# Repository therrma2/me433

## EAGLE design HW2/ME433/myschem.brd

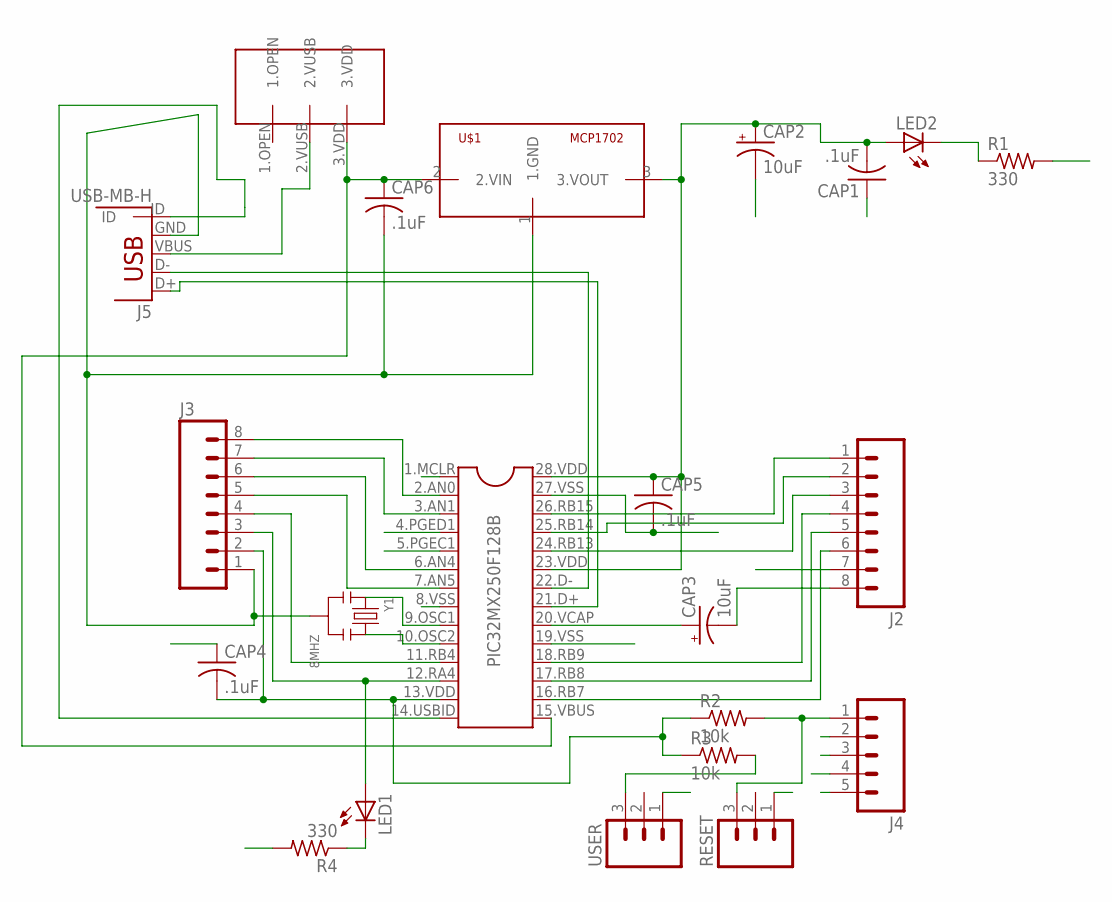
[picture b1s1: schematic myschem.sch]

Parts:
CAP1, CAP4, CAP5, CAP6: .1uF; C025-024X044
CAP2, CAP3: 10uF; B45181B
J2, J3: M08; 1X08_ROUND
J4: M05PTH; 1X05
J5: USB-MB-H
LED1, LED2: LED3MM
PIC32MX250F128B: DIL28-3
R1, R4: 330; 0207/10
R2, R3: 10k; 0207/10
RESET: M03PTH; 1X03
U$1: MCP1702; TO92
U$2: SLIDE-SWTICH; SLIDE-SWITCH
USER: M03PTH; 1X03
Y1: 8MHZ; X3-2.5-8X3X5.5MM

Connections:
GND: CAP1.1, CAP2.-, CAP3.-, CAP4.1, CAP5.2, CAP6.2, J2.8, J3.1, J4.3, J5.GND, PIC32MX250F128B.8.VSS (8), PIC32MX250F128B.19.VSS (19), PIC32MX250F128B.27.VSS (27), R1.2, R4.2, RESET.1, U$1.1 (1.GND), USER.1, Y1.2
MCLR: J4.1, PIC32MX250F128B.1.MCLR (1), R2.2, RESET.3
unnamed: J3.8, PIC32MX250F128B.2.AN0 (2)
unnamed: J3.7, PIC32MX250F128B.3.AN1 (3)
unnamed: J3.6, PIC32MX250F128B.6.AN4 (6)
unnamed: J3.5, PIC32MX250F128B.7.AN5 (7)
unnamed: J5.D-, PIC32MX250F128B.22.D- (22)
unnamed: J5.D+, PIC32MX250F128B.21.D+ (21)
unnamed: J3.3, LED1.A, PIC32MX250F128B.12.RA4 (12)
unnamed: J5.ID, PIC32MX250F128B.14.USBID (14)
unnamed: PIC32MX250F128B.9.OSC1 (9), Y1.1
unnamed: PIC32MX250F128B.10.OSC2 (10), Y1.3
unnamed: LED2.K (C), R1.1
unnamed: J5.VBUS, U$2.2.VUSB
unnamed: J2.6, PIC32MX250F128B.16.RB7 (16)
unnamed: LED1.K (C), R4.1
unnamed: J2.1, PIC32MX250F128B.26.RB15 (26)
unnamed: J2.2, PIC32MX250F128B.25.RB14 (25)
unnamed: J2.3, PIC32MX250F128B.24.RB13 (24)
unnamed: J2.4, PIC32MX250F128B.18.RB9 (18)
unnamed: J2.5, PIC32MX250F128B.17.RB8 (17)
unnamed: CAP3.+, PIC32MX250F128B.20.VCAP (20)
PGEC1: J4.5, PIC32MX250F128B.5.PGEC1 (5)
PGED1: J4.4, PIC32MX250F128B.4.PGED1 (4)
USER: J3.4, PIC32MX250F128B.11.RB4 (11), R3.2, USER.3
VBUS: CAP6.1, J2.7, PIC32MX250F128B.15.VBUS (15), U$1.2 (2.VIN), U$2.3.VDD
VDD: CAP1.2, CAP2.+, CAP4.2, CAP5.1, J3.2, J4.2, LED2.A, PIC32MX250F128B.13.VDD (13), PIC32MX250F128B.23.VDD (23), PIC32MX250F128B.28.VDD (28), R2.1, R3.1, U$1.3 (3.VOUT)

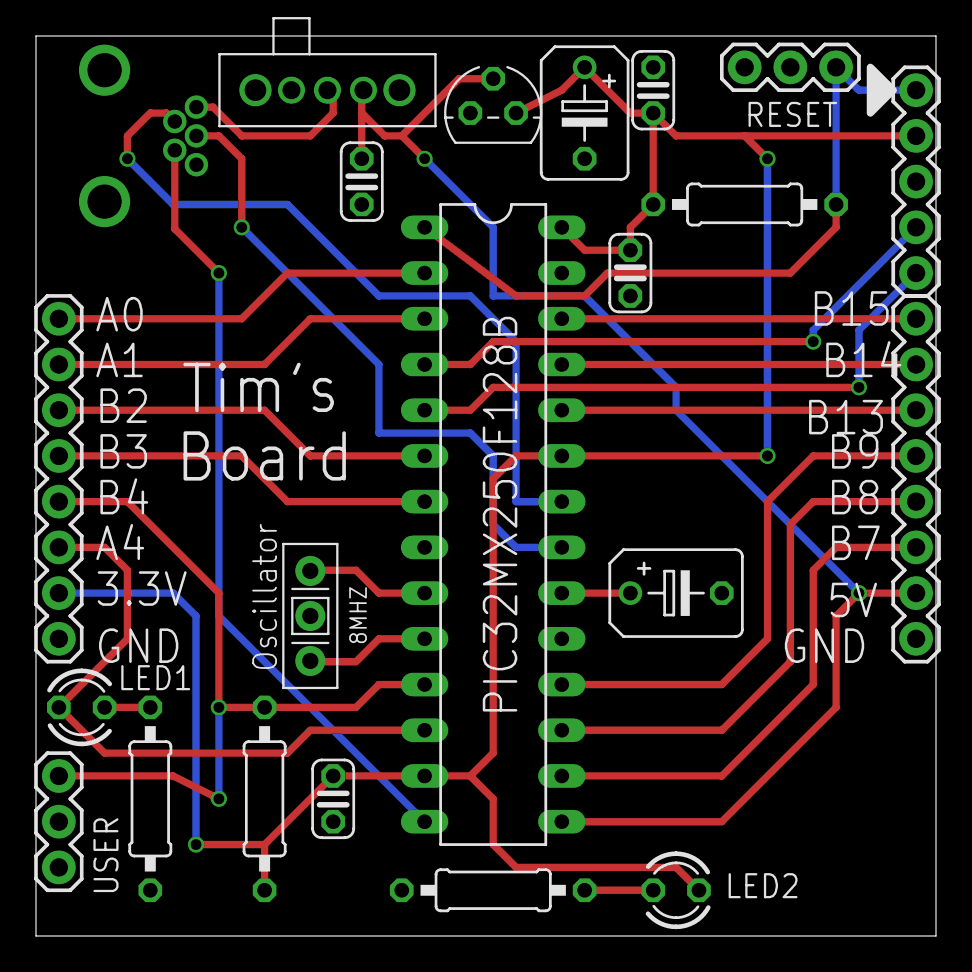
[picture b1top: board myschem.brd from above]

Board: 2 copper layers, 50.0 x 50.0 mm, 22 parts (0 on the bottom side), 27 nets.

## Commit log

2016-03-31 test
2016-03-31 Created project in MPLABX IDE with initial main.c file
2016-04-02 added #pragma commands for device config
2016-04-02 updated #pragma commands and added infinite loop to toggle LED at hopefully 1000 Hz
2016-04-04 Fixed while loop. Program now outputs a 100KHz square wave on pin RB2 (pin 6)
2016-04-04 Switched output pin to RA4 and added input pin to RB4
2016-04-04 updated while loop to only toggle at 1000KHz when the USER button is not pressed. When the button is pressed, the output pin is held at 0 and the light does not toggle.
2016-04-04 added a phot of voltage oscillations prior to adding capacitors and a photo of the full circuit.
2016-04-12 Started HW2 eagle cad library creation. finished PIC and voltage converter.
2016-04-13 Finished PCB design.
2016-04-14 cleaned up unnecesasry files in git
2016-04-14 added Gerber files and .brd
2016-04-14 Ready to be checked before order.
2016-04-14 Ready to be checked before order.
    uploaded correct files.
2016-04-25 Added new HW4 folder for SPI and I2C communication. copied existing main.c from HW1.
2016-04-25 created spi_init function
2016-04-25 testing setVoltage function
2016-04-25 added sine wave to DAC output A. working on triangle wave
2016-04-25 working sine and triangle waves at 10Hz, added screenshots of waveforms.
2016-04-30 added i2c master and slave functions.
2016-05-05 fixed I2C error
2016-05-05 added loop to toggle LED on pin expander when the expander input button is pressed.
2016-05-05 Added photo of working pin expander led
2016-05-05 working LCD. added text wrap when writing a string longer than the width of the screen.
2016-05-05 temporarily removed text wrap, added hello_world.jpg
2016-05-05 re-added text wrap
2016-05-05 Created HW6.X project for the IMU.
2016-05-05 able to read from the WHO_AM_I register and print the hex representation to the LCD
2016-05-05 7 registers (Gyro,acc, and temp) are being read and combined into 16 bit shorts. all 7 values are being written to the LCD, but are not correct yet. suspect an issue with the imu initialization.
2016-05-10 Added OC1 and OC2 initialization. OC1 and OC2 output PWMs that range from 0% to 100% over -1g to 1g on the x and y axes respectively. Addde dscreenshot of PWMs
2016-05-11 started android operations
2016-06-04 added IMU screenshot
2016-06-04 added pwm screenshot
2016-06-04 added hid_mouse homework #7
2016-06-04 added HW8
2016-06-04 added picCDC screenshot
2016-06-09 hw11
2016-06-09 box jpg
2016-06-09 HW12
2016-06-09 HW13
2016-06-09 HW15
2016-06-09 HW14
2016-06-09 HW16
